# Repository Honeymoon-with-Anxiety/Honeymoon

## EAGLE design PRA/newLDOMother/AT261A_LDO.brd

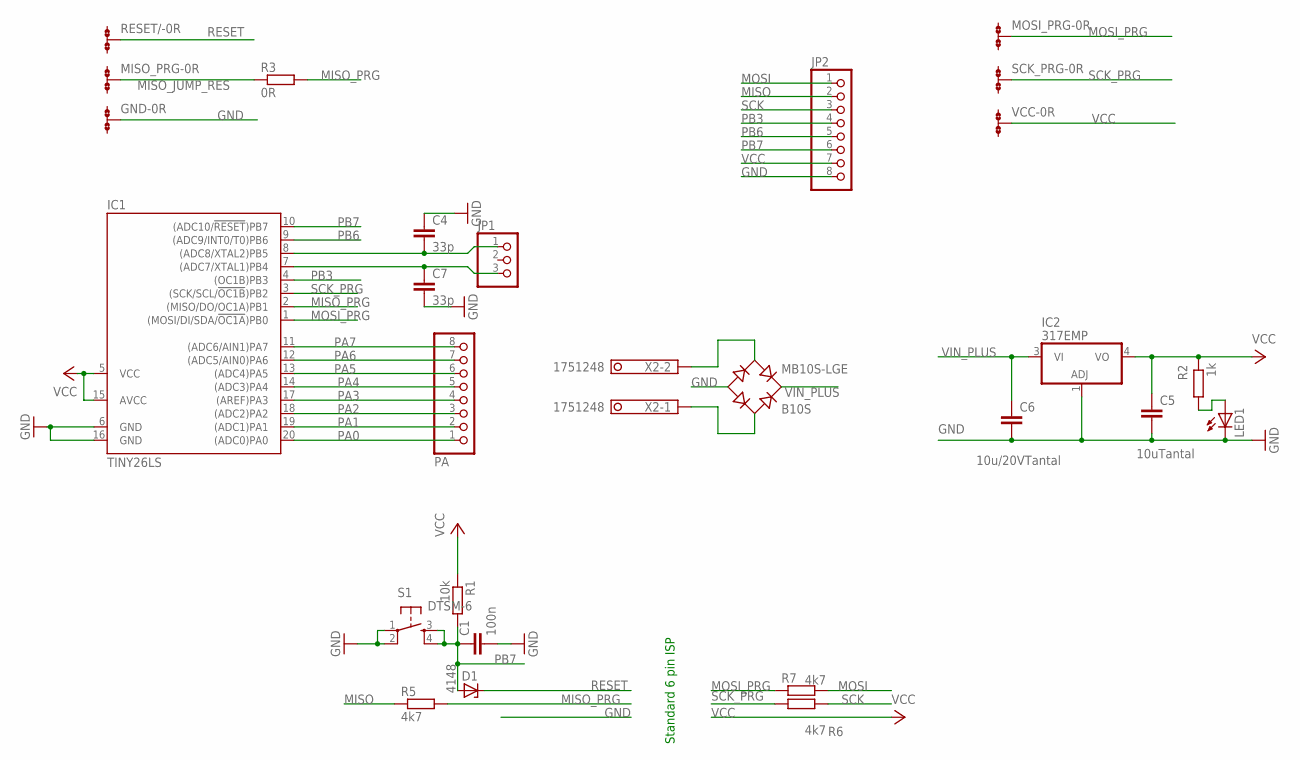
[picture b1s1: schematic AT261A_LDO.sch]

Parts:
C1: 100n; C1206
C4, C7: 33p; C1206
C5: 10uTantal; C1206K
C6: 10u/20VTantal; C1206K
D1: 4148; SMB
GND: 0R-JUMPA; A0R-JMP
IC1: TINY26LS; SO20L
IC2: 317EMP; SOT223
JP1: PINHD-1X3; 1X03
JP2: PINHD-1X8/90; 1X08/90
LED1: LEDSMT1206; 1206
MB10S-LGE: B10S; MBS
MISO_PRG: 0R-JUMPA; A0R-JMP
MOSI_PRG: 0R-JUMPA; A0R-JMP
PA: PINHD-1X8/90; 1X08/90
R1: 10k; R1206
R2: 1k; R1206
R3: 0R; M1406
R5, R6, R7: 4k7; R1206
RESET/: 0R-JUMPA; A0R-JMP
S1: DTSM-6
SCK_PRG: 0R-JUMPA; A0R-JMP
VCC: 0R-JUMPA; A0R-JMP
X2: 1751248

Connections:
GND: C1.2, C4.1, C5.2, C6.2, C7.2, GND.2, IC1.6 (GND), IC1.16 (GND), IC2.1 (ADJ), JP2.8, LED1.C, MB10S-LGE.-, S1.1, S1.2
MISO: JP2.2, R5.1
MISO_JUMP_RES: MISO_PRG.2, R3.1
MISO_PRG: IC1.2 ((MISO/DO/OC1A)PB1), R3.2, R5.2
MOSI: JP2.1, R7.2
MOSI_PRG: IC1.1 ((MOSI/DI/SDA/!OC1A!)PB0), MOSI_PRG.2, R7.1
unnamed: C4.2, IC1.8 ((ADC8/XTAL2)PB5), JP1.1
unnamed: C7.1, IC1.7 ((ADC7/XTAL1)PB4), JP1.3
unnamed: LED1.A, R2.1
PA0: IC1.20 ((ADC0)PA0), PA.1
PA1: IC1.19 ((ADC1)PA1), PA.2
PA2: IC1.18 ((ADC2)PA2), PA.3
PA3: IC1.17 ((AREF)PA3), PA.4
PA4: IC1.14 ((ADC3)PA4), PA.5
PA5: IC1.13 ((ADC4)PA5), PA.6
PA6: IC1.12 ((ADC5/AIN0)PA6), PA.7
PA7: IC1.11 ((ADC6/AIN1)PA7), PA.8
PB3: IC1.4 ((OC1B)PB3), JP2.4
PB6: IC1.9 ((ADC9/INT0/T0)PB6), JP2.5
PB7: C1.1, D1.A, IC1.10 ((ADC10/!RESET!)PB7), JP2.6, R1.2, S1.3, S1.4
RESET: D1.C, RESET/.2
SCK: JP2.3, R6.2
SCK_PRG: IC1.3 ((SCK/SCL/!OC1B!)PB2), R6.1, SCK_PRG.2
VCC: C5.1, IC1.5 (VCC), IC1.15 (AVCC), IC2.4 (VO), JP2.7, R1.1, R2.2, VCC.2
VIN_A: MB10S-LGE.AC1, X2.2
VIN_B: MB10S-LGE.AC2, X2.1
VIN_PLUS: C6.1, IC2.3 (VI), MB10S-LGE.+

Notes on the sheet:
Standard 6 pin ISP

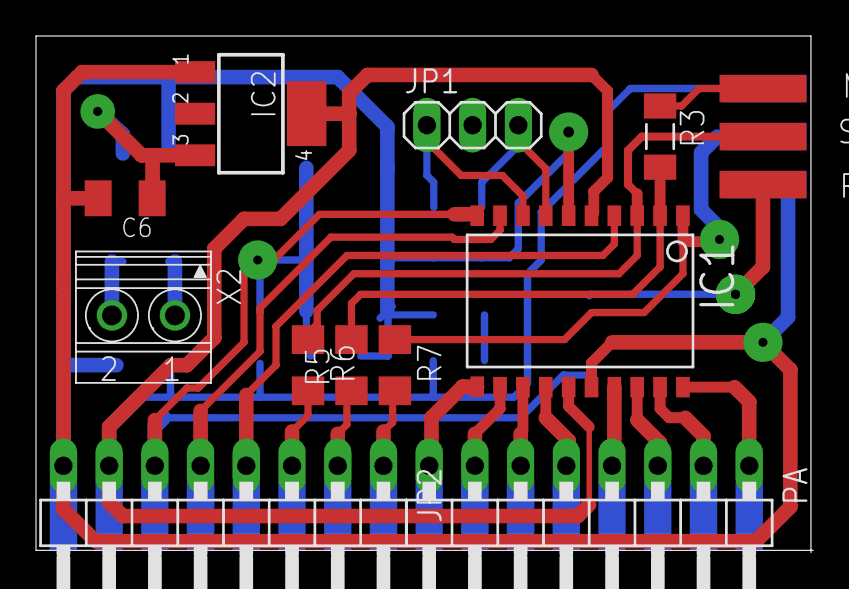
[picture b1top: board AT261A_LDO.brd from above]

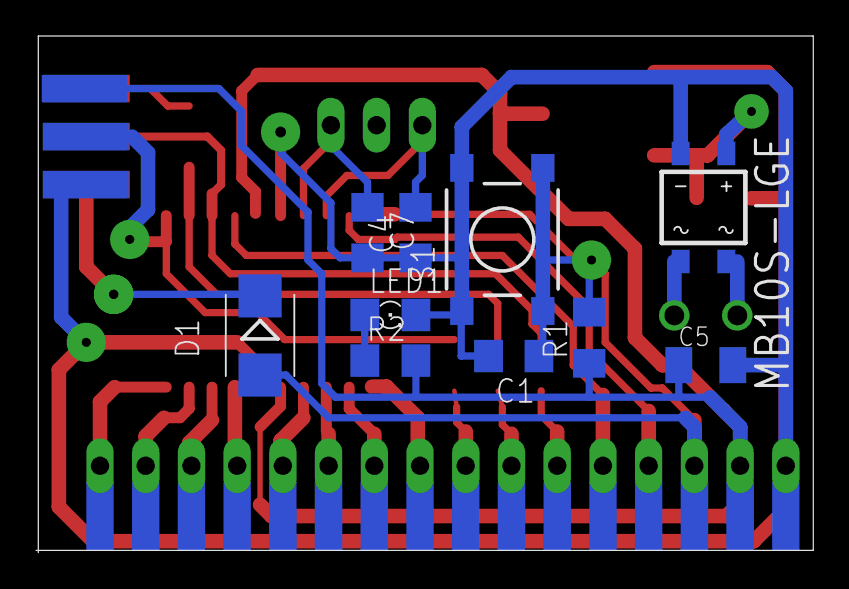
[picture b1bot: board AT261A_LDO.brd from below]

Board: 2 copper layers, 43.2 x 28.7 mm, 27 parts (13 on the bottom side), 27 nets.

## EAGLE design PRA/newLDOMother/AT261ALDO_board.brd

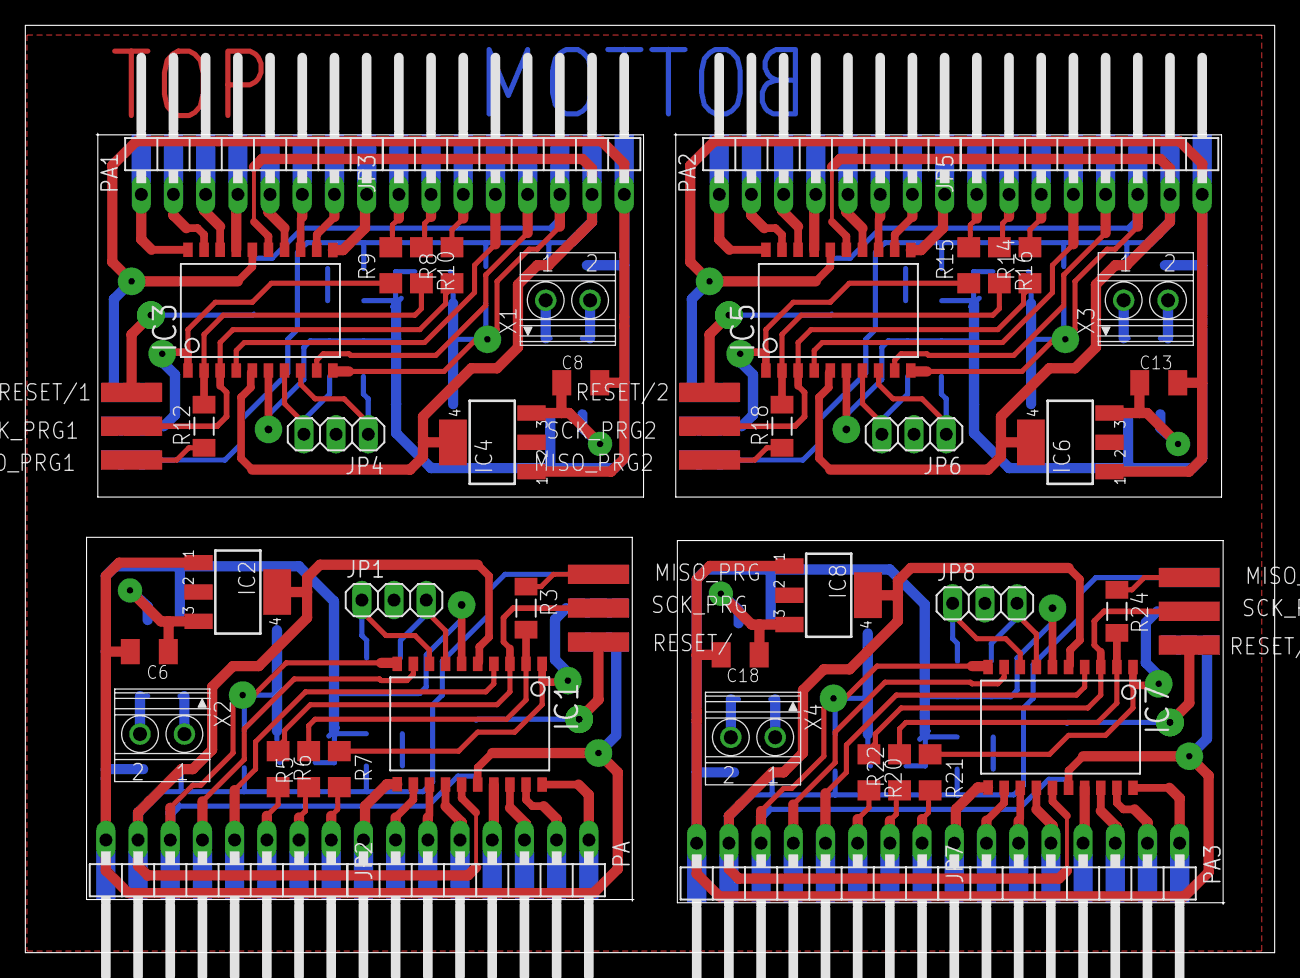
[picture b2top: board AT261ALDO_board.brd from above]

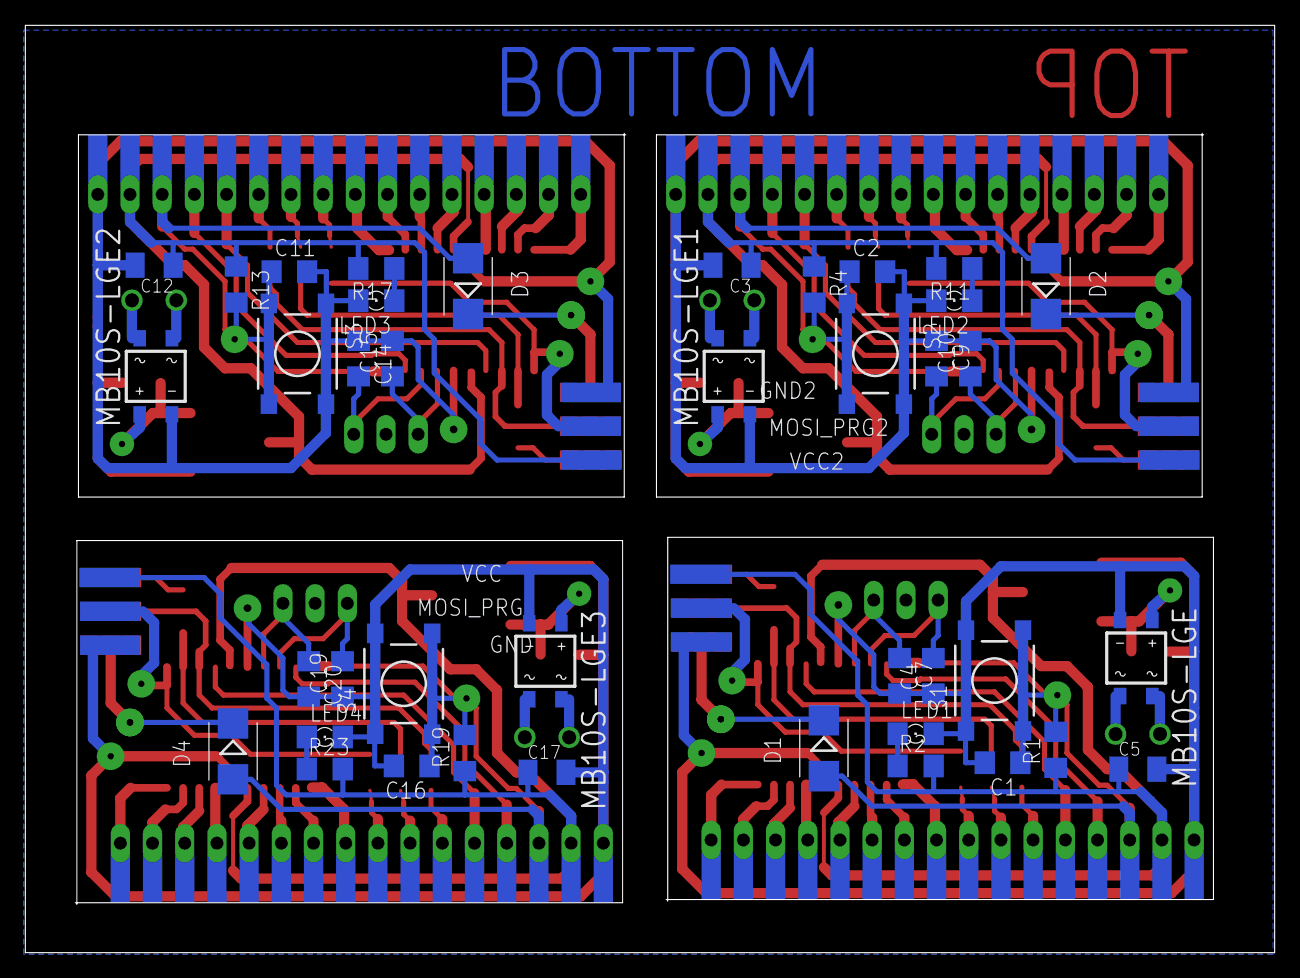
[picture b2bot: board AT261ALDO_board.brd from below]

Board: 2 copper layers, 98.6 x 73.2 mm, 108 parts (52 on the bottom side), 108 nets.

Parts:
C1, C2, C11, C16: 100n; C1206
C3, C5, C12, C17: 10uTantal; C1206K
C4, C7, C9, C10, C14, C15, C19, C20: 33p; C1206
C6, C8, C13, C18: 10u/20VTantal; C1206K
D1, D2, D3, D4: 4148; SMB
GND, GND1, GND2, GND3: 0R-JUMPA; A0R-JMP
IC1, IC3, IC5, IC7: TINY26LS; SO20L
IC2, IC4, IC6, IC8: 317EMP; SOT223
JP1, JP4, JP6, JP8: 1X03
JP2, JP3, JP5, JP7: 1X08/90
LED1, LED2, LED3, LED4: 1206
MB10S-LGE, MB10S-LGE1, MB10S-LGE2, MB10S-LGE3: B10S; MBS
MISO_PRG, MISO_PRG1, MISO_PRG2, MISO_PRG3: 0R-JUMPA; A0R-JMP
MOSI_PRG, MOSI_PRG1, MOSI_PRG2, MOSI_PRG3: 0R-JUMPA; A0R-JMP
PA, PA1, PA2, PA3: 1X08/90
R1, R4, R13, R19: 10k; R1206
R2, R11, R17, R23: 1k; R1206
R3, R12, R18, R24: 0R; M1406
R5, R6, R7, R8, R9, R10, R14, R15, R16, R20, R21, R22: 4k7; R1206
RESET/, RESET/1, RESET/2, RESET/3: 0R-JUMPA; A0R-JMP
S1, S2, S3, S4: DTSM-6
SCK_PRG, SCK_PRG1, SCK_PRG2, SCK_PRG3: 0R-JUMPA; A0R-JMP
VCC, VCC1, VCC2, VCC3: 0R-JUMPA; A0R-JMP
X1, X2, X3, X4: 1751248

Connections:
GND: C1.2, C4.1, C5.2, C6.2, C7.2, GND.2, IC1.6, IC1.16, IC2.1, JP2.8, LED1.C, MB10S-LGE.-, S1.1, S1.2
GND1: C2.2, C3.2, C8.2, C9.1, C10.2, GND1.2, IC3.6, IC3.16, IC4.1, JP3.8, LED2.C, MB10S-LGE1.-, S2.1, S2.2
GND2: C11.2, C12.2, C13.2, C14.1, C15.2, GND2.2, IC5.6, IC5.16, IC6.1, JP5.8, LED3.C, MB10S-LGE2.-, S3.1, S3.2
GND3: C16.2, C17.2, C18.2, C19.1, C20.2, GND3.2, IC7.6, IC7.16, IC8.1, JP7.8, LED4.C, MB10S-LGE3.-, S4.1, S4.2
MISO: JP2.2, R5.1
MISO1: JP3.2, R10.1
MISO2: JP5.2, R16.1
MISO3: JP7.2, R22.1
MISO_JUMP_RES: MISO_PRG.2, R3.1
MISO_JUMP_RES1: MISO_PRG1.2, R12.1
MISO_JUMP_RES2: MISO_PRG2.2, R18.1
MISO_JUMP_RES3: MISO_PRG3.2, R24.1
MISO_PRG: IC1.2, R3.2, R5.2
MISO_PRG1: IC3.2, R10.2, R12.2
MISO_PRG2: IC5.2, R16.2, R18.2
MISO_PRG3: IC7.2, R22.2, R24.2
MOSI: JP2.1, R7.2
MOSI1: JP3.1, R9.2
MOSI2: JP5.1, R15.2
MOSI3: JP7.1, R21.2
MOSI_PRG: IC1.1, MOSI_PRG.2, R7.1
MOSI_PRG1: IC3.1, MOSI_PRG1.2, R9.1
MOSI_PRG2: IC5.1, MOSI_PRG2.2, R15.1
MOSI_PRG3: IC7.1, MOSI_PRG3.2, R21.1
unnamed: C4.2, IC1.8, JP1.1
unnamed: C9.2, IC3.8, JP4.1
unnamed: C7.1, IC1.7, JP1.3
unnamed: LED1.A, R2.1
unnamed: C10.1, IC3.7, JP4.3
unnamed: LED2.A, R11.1
unnamed: C14.2, IC5.8, JP6.1
unnamed: C15.1, IC5.7, JP6.3
unnamed: LED3.A, R17.1
unnamed: C19.2, IC7.8, JP8.1
unnamed: C20.1, IC7.7, JP8.3
unnamed: LED4.A, R23.1
PA0: IC1.20, PA.1
PA1: IC1.19, PA.2
PA2: IC1.18, PA.3
PA3: IC1.17, PA.4
PA4: IC1.14, PA.5
PA5: IC1.13, PA.6
PA6: IC1.12, PA.7
PA7: IC1.11, PA.8
PA8: IC3.20, PA1.1
PA9: IC3.19, PA1.2
PA10: IC3.18, PA1.3
PA11: IC3.17, PA1.4
PA12: IC3.14, PA1.5
PA13: IC3.13, PA1.6
PA14: IC3.12, PA1.7
PA15: IC3.11, PA1.8
PA16: IC5.20, PA2.1
PA17: IC5.19, PA2.2
PA18: IC5.18, PA2.3
PA19: IC5.17, PA2.4
PA20: IC5.14, PA2.5
PA21: IC5.13, PA2.6
PA22: IC5.12, PA2.7
PA23: IC5.11, PA2.8
PA24: IC7.20, PA3.1
PA25: IC7.19, PA3.2
PA26: IC7.18, PA3.3
PA27: IC7.17, PA3.4
PA28: IC7.14, PA3.5
PA29: IC7.13, PA3.6
PA30: IC7.12, PA3.7
PA31: IC7.11, PA3.8
PB1: IC3.4, JP3.4
PB2: IC3.9, JP3.5
PB3: IC1.4, JP2.4
PB4: C2.1, D2.A, IC3.10, JP3.6, R4.2, S2.3, S2.4
PB5: IC5.4, JP5.4
PB6: IC1.9, JP2.5
PB7: C1.1, D1.A, IC1.10, JP2.6, R1.2, S1.3, S1.4
PB8: IC5.9, JP5.5
PB9: C11.1, D3.A, IC5.10, JP5.6, R13.2, S3.3, S3.4
PB10: IC7.4, JP7.4
PB11: IC7.9, JP7.5
PB12: C16.1, D4.A, IC7.10, JP7.6, R19.2, S4.3, S4.4
RESET: D1.C, RESET/.2
RESET1: D2.C, RESET/1.2
RESET2: D3.C, RESET/2.2
RESET3: D4.C, RESET/3.2
SCK: JP2.3, R6.2
SCK1: JP3.3, R8.2
SCK2: JP5.3, R14.2
SCK3: JP7.3, R20.2
SCK_PRG: IC1.3, R6.1, SCK_PRG.2
SCK_PRG1: IC3.3, R8.1, SCK_PRG1.2
SCK_PRG2: IC5.3, R14.1, SCK_PRG2.2
SCK_PRG3: IC7.3, R20.1, SCK_PRG3.2
VCC: C5.1, IC1.5, IC1.15, IC2.4, JP2.7, R1.1, R2.2, VCC.2
VCC1: C3.1, IC3.5, IC3.15, IC4.4, JP3.7, R4.1, R11.2, VCC1.2
VCC2: C12.1, IC5.5, IC5.15, IC6.4, JP5.7, R13.1, R17.2, VCC2.2
VCC3: C17.1, IC7.5, IC7.15, IC8.4, JP7.7, R19.1, R23.2, VCC3.2
VIN_A: MB10S-LGE.AC1, X2.2
VIN_A1: MB10S-LGE1.AC1, X1.2
VIN_A2: MB10S-LGE2.AC1, X3.2
VIN_A3: MB10S-LGE3.AC1, X4.2
VIN_B: MB10S-LGE.AC2, X2.1
VIN_B1: MB10S-LGE1.AC2, X1.1
VIN_B2: MB10S-LGE2.AC2, X3.1
VIN_B3: MB10S-LGE3.AC2, X4.1
VIN_PLUS: C6.1, IC2.3, MB10S-LGE.+
VIN_PLUS1: C8.1, IC4.3, MB10S-LGE1.+
VIN_PLUS2: C13.1, IC6.3, MB10S-LGE2.+
VIN_PLUS3: C18.1, IC8.3, MB10S-LGE3.+

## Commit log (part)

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2024-03-13 TVP_13_3_24
2024-03-14 Mluv_14_3_24
2024-03-14 Lit_14_3_24
2024-03-17 Lit_15_3_24
2024-03-17 Lit_17_11_24
2024-03-19 TVP_19_3_24
2024-03-20 Lit_20_3_24
2024-03-22 TVP_20_3_24
2024-03-22 Lit_22_3_24
2024-03-24 Lit_24_3_24
2024-03-24 SIZ_24_3_24
2024-03-25 ELM_25_3_24
2024-03-26 SIZ_26_3_24
2024-03-26 TVP_26_3_24
2024-03-26 ELM_26_3_24
2024-03-27 SIZ_27_3_24
2024-03-27 Lit_27_3_24
2024-04-02 Anxitety_31_3_24
2024-04-02 ELM_31_3_24
2024-04-02 TVP_2_4_24
2024-04-02 SIZ_2_4_24
2024-04-03 Lit_3_4_24
2024-04-03 ELM_3_4_24
2024-04-04 Mluv_4_4_24
2024-04-04 ELM_4_4_24
2024-04-04 SIZ_4_4_24
2024-04-05 Lit_5_4_24
2024-04-06 ELM_6_4_24
2024-04-07 Lit_7_4_24
2024-04-08 ELM_8_4_24
2024-04-08 TVP_8_4_24
2024-04-10 TVP_9_4_24
2024-04-10 Lit_10_4_24
2024-04-10 SPV_10_4_24
2024-04-11 Mluv_11_4_24
2024-04-11 SIZ_11_4_24
2024-04-13 Lit_12_4_24
2024-04-13 ELM_13_4_24
2024-04-15 ELM_15_4_24
2024-04-15 MIT_15_4_24
2024-04-15 TVP_15_4_24
2024-04-16 TVP_16_4_24
2024-04-17 Lit_17_4_24
2024-04-17 MIT_17_4_24
2024-04-19 Lit_17_3_24
2024-04-20 ELM_19_4_24
2024-04-20 ELM_20_4_24
2024-04-21 ELM_21_4_24
2024-04-22 ELM_22_4_24
2024-04-23 TVP_23_4_24
2024-04-24 Lit_24_4_24
2024-04-25 MIT_24_4_24
2024-04-25 Mluv_25_4_24
2024-04-25 ELM_25_4_24
2024-04-25 ELM_25_4_24
    Poté, co jsem Pičmanovi zandal combo jsem si musel dát sušenku aneb Fancy way jak se dostat ke stejnému výsledku
2024-04-27 ELM_27_4_24
2024-04-28 Lit_26_4_24
2024-05-02 MIT_29_4_24
2024-05-02 TVP_2_5_24
2024-05-02 SIZ_2_5_24
2024-05-03 ČJL_3_5_24
2024-05-06 ELM_6_5_24
2024-05-07 TVP_7_5_24
2024-05-09 SIZ_9_5_24
2024-05-09 ELM_9_5_24
2024-05-10 ELT_10_5_24
2024-05-12 ELM_12_5_24
2024-05-12 Lit_12_5_24
2024-05-13 ELM_13_5_24
2024-05-13 Lit_13_5_24
2024-05-13 ELT_13_5_24
2024-05-14 TVP_14_5_24
2024-05-14 ELT_14_5_24
2024-05-14 SIZ_14_5_24
2024-05-15 TVP_15_5_24
2024-05-15 ELT_15_5_24
2024-05-15 SPV_15_5_24
2024-05-17 Mluv_16_5_24
2024-05-17 Lit_17_5_24
2024-06-05 24w23
2024-06-07 TVP_7_6_24
2024-06-10 ELM_10_6_24
2024-06-10 TVP_10_6_24
2024-06-11 TVP_11_6_24
2024-06-12 Lit_12_6_24
2024-06-12 MIT_12_6_24
2024-06-12 ELM_12_6_24
2024-06-13 Mluv_13_6_24
2024-06-14 ELM_14_6_24
2024-06-17 ELM_17_6_24
2024-06-18 SIZ_18_6_24
2024-06-18 ELM_18_6_24
2024-06-19 SIZ_19_6_24
2024-06-19 TVP_19_6_24
2024-06-19 Lit_19_6_24
2024-06-20 Mluv_20_6_24
2024-06-20 ELM_20_6_24
2024-06-21 Lit_21_6_24
2024-06-27 ELT_27_6_24
2024-07-01 ELT_1_7_24
2024-07-01 24w27
2024-08-28 Anxiety
2024-09-05 TVP_5_9_24
2024-09-05 AJ_5_9_24
2024-09-10 EKO_9_9_24
2024-09-10 MIT_6_9_24
2024-09-10 SPV_6_9_24
2024-09-10 Meta_10_9_24
2024-09-10 Lit_10_9_24
2024-09-15 AJ_11_9_24
2024-09-15 TVP_12_9_24
2024-09-15 TVP_15_9_24
2024-09-16 TVP_16_9_24
2024-09-17 Lit_17_9_24
2024-09-19 TVP_19_9_24
2024-09-19 AJ_19_9_24
2024-09-20 SPV_20_9_24
2024-09-22 SPV_22_9_24
2024-09-22 TVP_22_9_24
2024-09-22 Lit_22_9_24
2024-09-22 AJ_22_9_24
2024-09-23 TVP_23_9_24
2024-09-23 EKO_23_9_24
2024-09-25 Lit_24_9_24
2024-09-25 Mluv_25_9_24
2024-09-25 TVP_25_9_24
2024-09-26 TVP_26_9_24
2024-09-27 SPV_27_9_24
2024-09-28 EKO_28_9_24
2024-09-29 Lit_29_9_24
2024-09-29 TVP_29_9_24
2024-09-30 Lit_30_9_24
2024-09-30 TVP_30_9_24
2024-10-08 TVP_8_10_24
2024-10-09 TVP_9_10_24
2024-10-11 Lit_10_10_24
2024-10-12 Lit_11_10_24
2024-10-12 Lit_12_10_24
2024-10-12 ČJL_12_10_24
2024-10-13 TVP_13_10_24
2024-10-14 TVP_14_10_24
2024-10-15 EKO_15_10_24
2024-10-16 TVP_15_10_24
2024-10-16 EKO_16_10_24
2024-10-17 TVP_17_10_24
2024-10-19 TVP_19_10_24
2024-10-21 TVP_20_10_24
2024-10-21 TVP_21_10_24
2024-10-21 EKO_21_10_24
2024-10-22 EKO_22_10_24
2024-10-25 MIT_25_10_24
2024-10-31 TVP_30_10_24
2024-10-31 TVP_31_10_24
2024-11-03 Lit_3_11_24
2024-11-04 Lit_4_11_24
2024-11-05 TVP_4_11_24
2024-11-05 Lit_5_11_24
2024-11-05 TVP_5_11_24
2024-11-06 PVP_29_9_24
2024-11-06 PVP_6_11_24
2024-11-06 TVP_6_11_24
2024-11-07 TVP_7_11_24
2024-11-07 SPV_7_11_24
2024-11-08 TVP_8_11_24
2024-11-08 MIT_8_11_24
2024-11-08 SPV_8_11_24
2024-11-10 SPV_10_11_24
2024-11-11 Lit_11_11_24
2024-11-11 TVP_11_11_24
2024-11-13 Mluv_13_11_24
2024-11-13 Lit_12_11_24
2024-11-15 MIT_15_11_24
2024-11-15 SPV_15_11_24
2024-11-18 TVP_18:_11_24
2024-11-19 Lit_19_11_24
2024-11-20 Mluv_20_11_24
2024-11-20 TVP_20_11_24
2024-11-21 TVP_21_11_24
2024-11-21 ČJL_21_11_24
2024-11-22 SPV_22_11_24
2024-11-22 Revert "SPV_22_11_24"
    This reverts commit 7f084632e85f1778f0df26d469b2df890bc7a77c.
2024-11-22 MIT_22_11_24
2024-11-23 MIT_23_11_24
2024-11-24 MIT_24_11_24
2024-11-24 TVP_24_11_24
2024-11-25 Lit_25_11_24
2024-11-25 MIT_25_11_24
2024-11-26 MIT_26_11_24
2024-11-26 ČJL_26_11_24
2024-11-27 Mluv_27_11_24
2024-11-27 Meta_27_11_24
2024-11-27 MIT_27_11_24
2024-11-28 SPV_28_11_24
2024-11-29 SPV_29_11_24
2024-12-01 Lit_1_12_24
2024-12-02 ČJL_2_12_24
2024-12-05 MIT_2_12_24
2024-12-05 TVP_5_12_24
2024-12-05 SPV_5_12_24
2024-12-06 MIT_6_12_24
2024-12-10 Lit_10_12_24
2024-12-12 Mluv_11_12_24
2024-12-12 Honeymoon
2024-12-12 MIT_12_12_24
2024-12-13 SPV_13_12_24
2024-12-13 TVP_12_12_24
2024-12-13 TVP_13_12_24
2024-12-15 TVP_15_12_24
2024-12-15 PVP_15_12_24
2024-12-16 Lit_16_12_24
2024-12-17 TVP_16_12_24
2024-12-17 Lit_17_12_24
2024-12-18 Mluv_18_12_24
2024-12-20 TVP_20_12_24
2024-12-31 TVP_31_12_24
2025-01-01 TVP_1_1_25
2025-01-03 Lit_3_1_24
2025-01-04 Lit_4_1_25
2025-01-05 Lit_5_1_25
2025-01-06 Lit_6_1_25
2025-01-07 Lit_7_1_25
2025-01-07 EKO_7_1_25
2025-01-08 EKO_8_1_25
2025-01-09 Mluv_8_1_25
2025-01-13 Lit_13_1_25
2025-01-14 Mluv_14_1_25
2025-01-15 SPV_15_1_25
2025-01-16 SPV_16_1_25
2025-01-16 Mluv_15_1_25
2025-01-18 MIT_17_1_25
2025-01-18 SPV_17_1_25
2025-01-20 Lit_20_1_25
2025-01-20 EKO_20_1_25
2025-01-22 Lit_21_1_25
2025-01-22 TVP_22_1_25
2025-01-23 TVP_23_1_25
2025-01-27 EKO_27_1_25
2025-01-30 25w05
2025-02-02 Mluv_2_2_25
2025-02-03 EKO_3_2_25
2025-02-04 Mluv_4_2_25
2025-02-05 Mluv_5_2_25
2025-02-07 MIT_7_2_25
2025-02-08 Lit_8_2_25
2025-02-10 Lit_10_2_25
2025-02-11 EKO_10_2_25
2025-02-11 EKO_11_2_25
2025-02-11 Lit_11_2_25
2025-02-12 Mluv_12_2_25
2025-02-13 EKO_13_2_25
2025-02-24 Lit_24_2_25
2025-02-24 EKO_24_2_25
2025-02-25 EKO_25_2_25
2025-02-26 Mluv_26_2_25
2025-02-28 MIT_28_2_25
2025-02-28 Revert "MIT_28_2_25"
    This reverts commit 712a4d767a55165df9ee441e1d11eeb5089b3d9f.
2025-03-03 SPV_28_2_25
2025-03-03 Lit_3_3_25
2025-03-03 EKO_3_3_25
2025-03-04 Lit_4_3_25
2025-03-06 TVP_6_3_25
2025-03-07 MIT_7_3_25
2025-03-10 Lit_10_3_25
2025-03-10 EKO_10_3_25
2025-03-11 Mluv_11_3_25
2025-03-12 Lit_11_3_25
2025-03-12 Mluv_12_3_25
2025-03-13 TVP_13_3_25
2025-03-13 Mluv_13_3_25
2025-03-14 SPV_14_3_25
2025-03-16 Mluv_16_3_25
2025-03-17 Mluv_17_3_25
2025-03-18 Mluv_18_3_25
2025-03-19 TVP_17_3_25
2025-03-19 EKO_17_3_25
2025-03-19 Mluv_19_3_25
2025-03-19 MIT_19_3_25
2025-03-20 MIT_20_3_25
2025-03-21 EKO_20_3_25
2025-03-21 MIT_21_3_25
2025-03-21 SPV_21_3_25
2025-03-22 EKO_22_3_25
2025-03-24 Lit_24_3_25
2025-03-24 TVP_24_3_25
2025-03-25 EKO_24_3_25
2025-03-25 Lit_25_3_25
2025-03-27 TVP_27_3_25
2025-03-28 SPV_28_3_25
2025-03-31 TVP_31_3_25
2025-03-31 Lit_31_3_25
2025-04-01 EKO_31_3_25
2025-04-01 Lit_1_4_25
2025-04-03 MIT_3_4_25
2025-04-03 EKO_3_4_25
2025-04-04 MIT_4_4_25
2025-04-07 Lit_7_4_25
2025-04-07 Mluv_7_4_25
2025-04-08 Lit_8_4_25
2025-04-08 Mluv_8_4_25
2025-04-09 Lit_9_4_25
2025-04-09 MIT_9_4_25
2025-04-10 MIT_10_4_25
2025-04-11 MIT_11_4_25
2025-04-11 SPV_11_4_25
2025-04-14 MIT_14_4_25
2025-04-15 Lit_15_4_25
2025-04-16 Lit_16_4_25
2025-04-21 MIT_21_4_25
2025-04-22 Lit_22_4_25
2025-04-25 ČJL_25_4_25
2025-04-28 ČJL_28_4_25
2025-05-21 Anxiety
    Kradez
2025-05-21 Anxiety
    MAT
